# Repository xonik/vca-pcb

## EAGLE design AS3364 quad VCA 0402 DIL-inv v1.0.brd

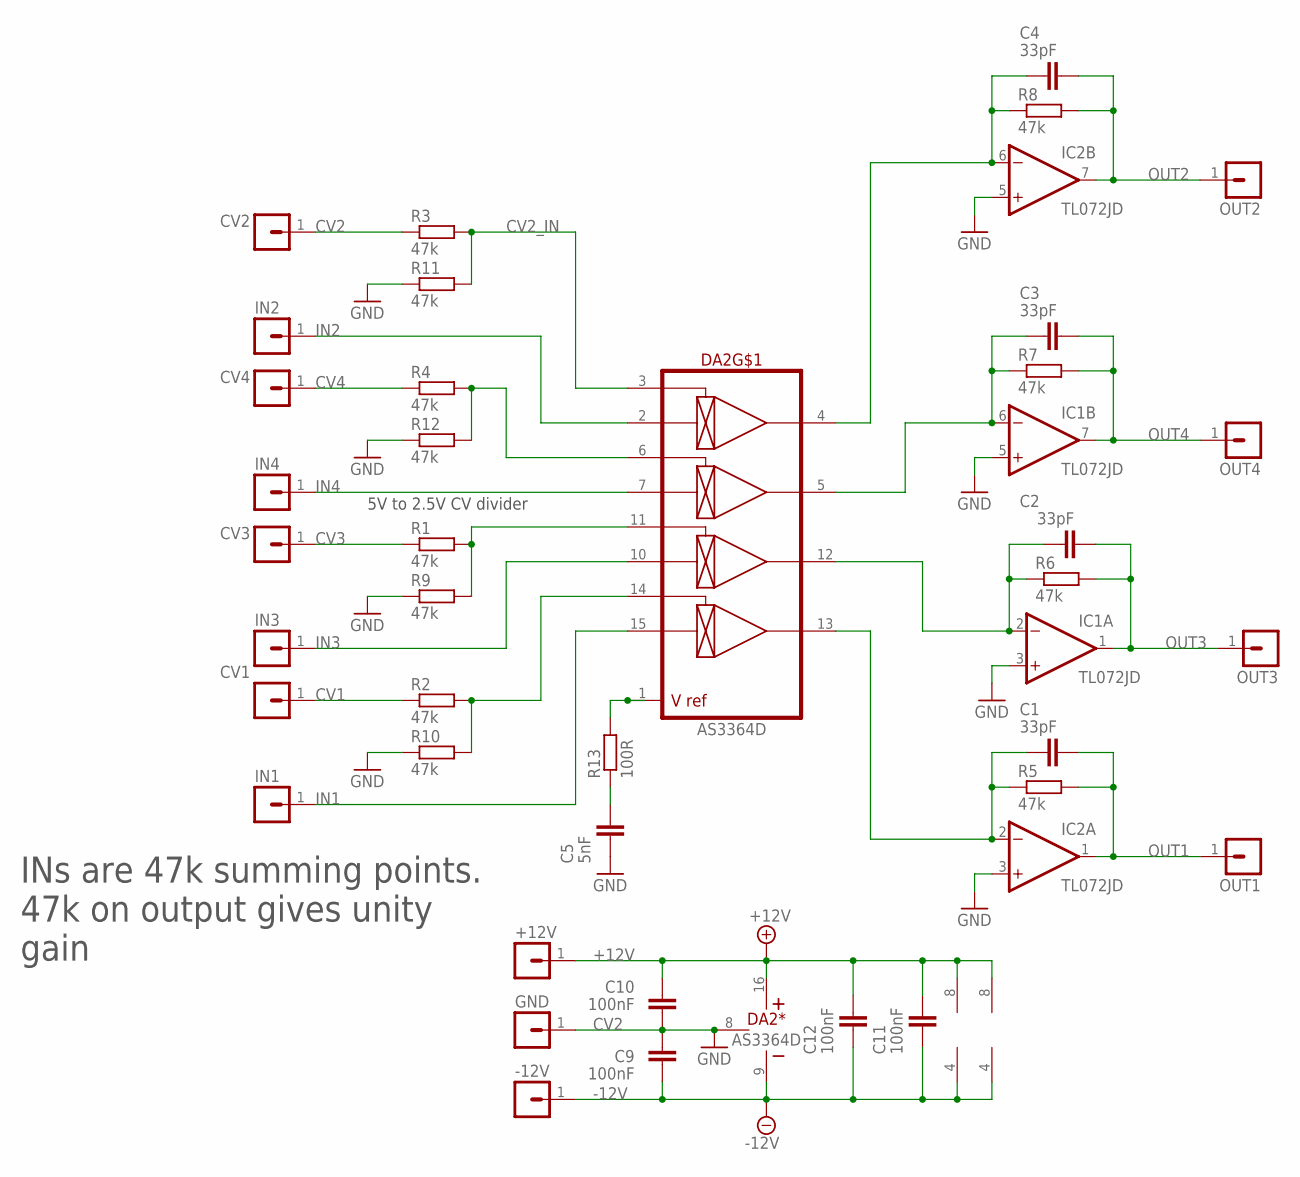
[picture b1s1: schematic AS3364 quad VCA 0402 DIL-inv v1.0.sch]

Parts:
+12V: MA01-1JP; SIP-PIN01-1J
-12V: MA01-1JP; SIP-PIN01-1J
C1, C2, C3, C4: 33pF; C0402
C5: 5nF; C0402
C9, C10, C11, C12: 100nF; C0402
CV1, CV2, CV3, CV4: MA01-1JP; SIP-PIN01-1J
DA2: AS3364D; DIL16J
GND: MA01-1JP; SIP-PIN01-1J
IC1, IC2: TL072JD; SO08J
IN1, IN2, IN3, IN4: MA01-1JP; SIP-PIN01-1J
OUT1, OUT2, OUT3, OUT4: MA01-1JP; SIP-PIN01-1J
R1, R2, R3, R4, R5, R6, R7, R8, R9, R10, R11, R12: 47k; R0402
R13: 100R; R0402

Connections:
+12V: +12V.1, C10.2, C11.2, C12.2, DA2.16 (V+), IC1.8 (V+), IC2.8 (V+)
-12V: -12V.1, C9.1, C11.1, C12.1, DA2.9 (V-), IC1.4 (V-), IC2.4 (V-)
CV1: CV1.1, R2.1
CV2: CV2.1, R3.1
CV2_IN: DA2.3 (CV1), R3.2, R11.2
CV3: CV3.1, R1.1
CV4: CV4.1, R4.1
GND: C5.1, C9.2, C10.1, DA2.8 (GND), GND.1, IC1.3 (+IN), IC1.5 (+IN), IC2.3 (+IN), IC2.5 (+IN), R9.1, R10.1, R11.1, R12.1
IN1: DA2.15 (IN4), IN1.1
IN2: DA2.2 (IN1), IN2.1
IN3: DA2.10 (IN3), IN3.1
IN4: DA2.7 (IN2), IN4.1
unnamed: C4.1, DA2.4 (OUT1), IC2.6 (-IN), R8.1
unnamed: DA2.1 (VREF), R13.2
unnamed: C3.1, DA2.5 (OUT2), IC1.6 (-IN), R7.1
unnamed: C2.1, DA2.12 (OUT3), IC1.2 (-IN), R6.1
unnamed: C1.1, DA2.13 (OUT4), IC2.2 (-IN), R5.1
unnamed: DA2.6 (CV2), R4.2, R12.2
unnamed: DA2.11 (CV3), R1.2, R9.2
unnamed: C5.2, R13.1
unnamed: DA2.14 (CV4), R2.2, R10.2
OUT1: C1.2, IC2.1 (OUT), OUT1.1, R5.2
OUT2: C4.2, IC2.7 (OUT), OUT2.1, R8.2
OUT3: C2.2, IC1.1 (OUT), OUT3.1, R6.2
OUT4: C3.2, IC1.7 (OUT), OUT4.1, R7.2

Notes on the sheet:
INs are 47k summing points. 47k on output gives unity gain
5V to 2.5V CV divider

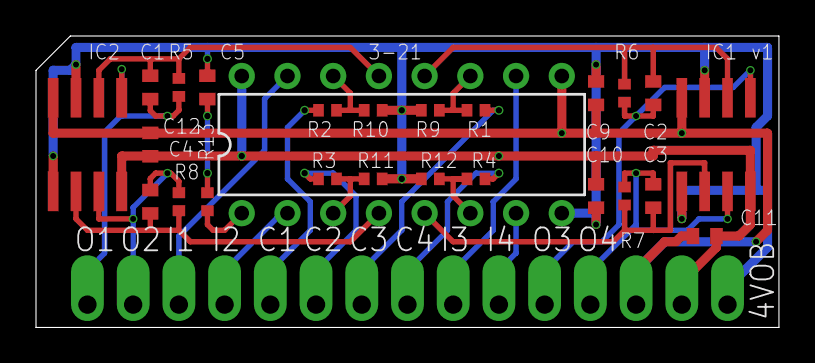
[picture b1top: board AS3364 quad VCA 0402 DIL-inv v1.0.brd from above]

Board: 2 copper layers, 41.3 x 16.2 mm, 41 parts (1 on the bottom side), 25 nets.

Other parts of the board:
U$1: XONIK_LOGO_18

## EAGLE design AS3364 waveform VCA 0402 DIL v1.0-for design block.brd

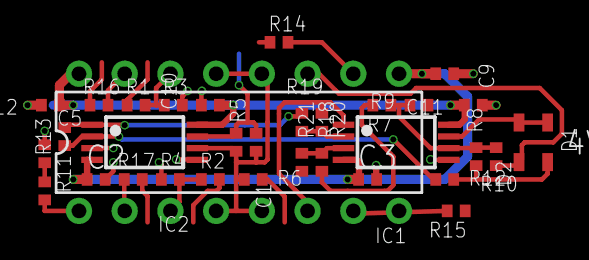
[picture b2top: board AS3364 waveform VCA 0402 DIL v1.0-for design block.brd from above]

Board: 2 copper layers, 35 parts (1 on the bottom side), 23 nets.

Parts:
C1: 33pF; C0402-J
C2, C3, C9, C10, C11, C12: 1uF; C0402-J
C5: 5nF; C0402-J
D1, D2: SOD323J
DA2: AS3364D; DIL16J
IC1, IC2: TL072JT; TSSOP8J
R1, R2: 33k; R0402
R3, R4: 22k; R0402
R5, R6, R14, R15, R16, R17: 47k; R0402
R7, R11, R18, R19: 25k; R0402
R8, R10, R20, R21: 20k; R0402
R9: 50k; R0402
R12: 10k; R0402
R13: 100R; R0402
U$1: XONIK_LOGO_18

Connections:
+12V: C10.2, C11.2, C12.2, DA2.16, IC1.8, IC2.8
-12V: C2.1, C3.1, C9.1, DA2.9, IC1.4, IC2.4
AGND: C2.2, C3.2, C5.1, C9.2, C10.1, C11.1, C12.1, DA2.8, IC1.5, IC2.3, IC2.5, R3.1, R4.1, R21.1
MIX_BUS: C1.2, DA2.4, DA2.5, DA2.12, DA2.13, IC2.6, R5.2, R6.1
unnamed: DA2.1, R13.2
unnamed: D1.1, D2.2, IC1.7
unnamed: IC1.6, R7.2, R8.1, R9.2, R10.1
unnamed: IC1.3, R18.2, R21.2
unnamed: C5.2, R13.1
unnamed: IC1.2, R19.2, R20.1
unnamed: IC2.2, R11.1, R12.2
unnamed: D1.2, R8.2, R12.1
OUT: C1.1, IC2.7, R5.1
PAN_CV: R7.1, R18.1
PULSE_CV: IC2.1, R11.2, R19.1
SAW_CV: DA2.6, IC1.1, R20.2
SAW_IN: DA2.7, R15.2
SUB1_CV_IN: DA2.14, R1.2, R3.2
SUB1_IN: DA2.15, R16.2
SUB2_CV_IN: DA2.3, R2.2, R4.2
SUB2_IN: DA2.2, R17.2
TRI_CV: D2.1, DA2.11, R10.2
TRI_IN: DA2.10, R14.2

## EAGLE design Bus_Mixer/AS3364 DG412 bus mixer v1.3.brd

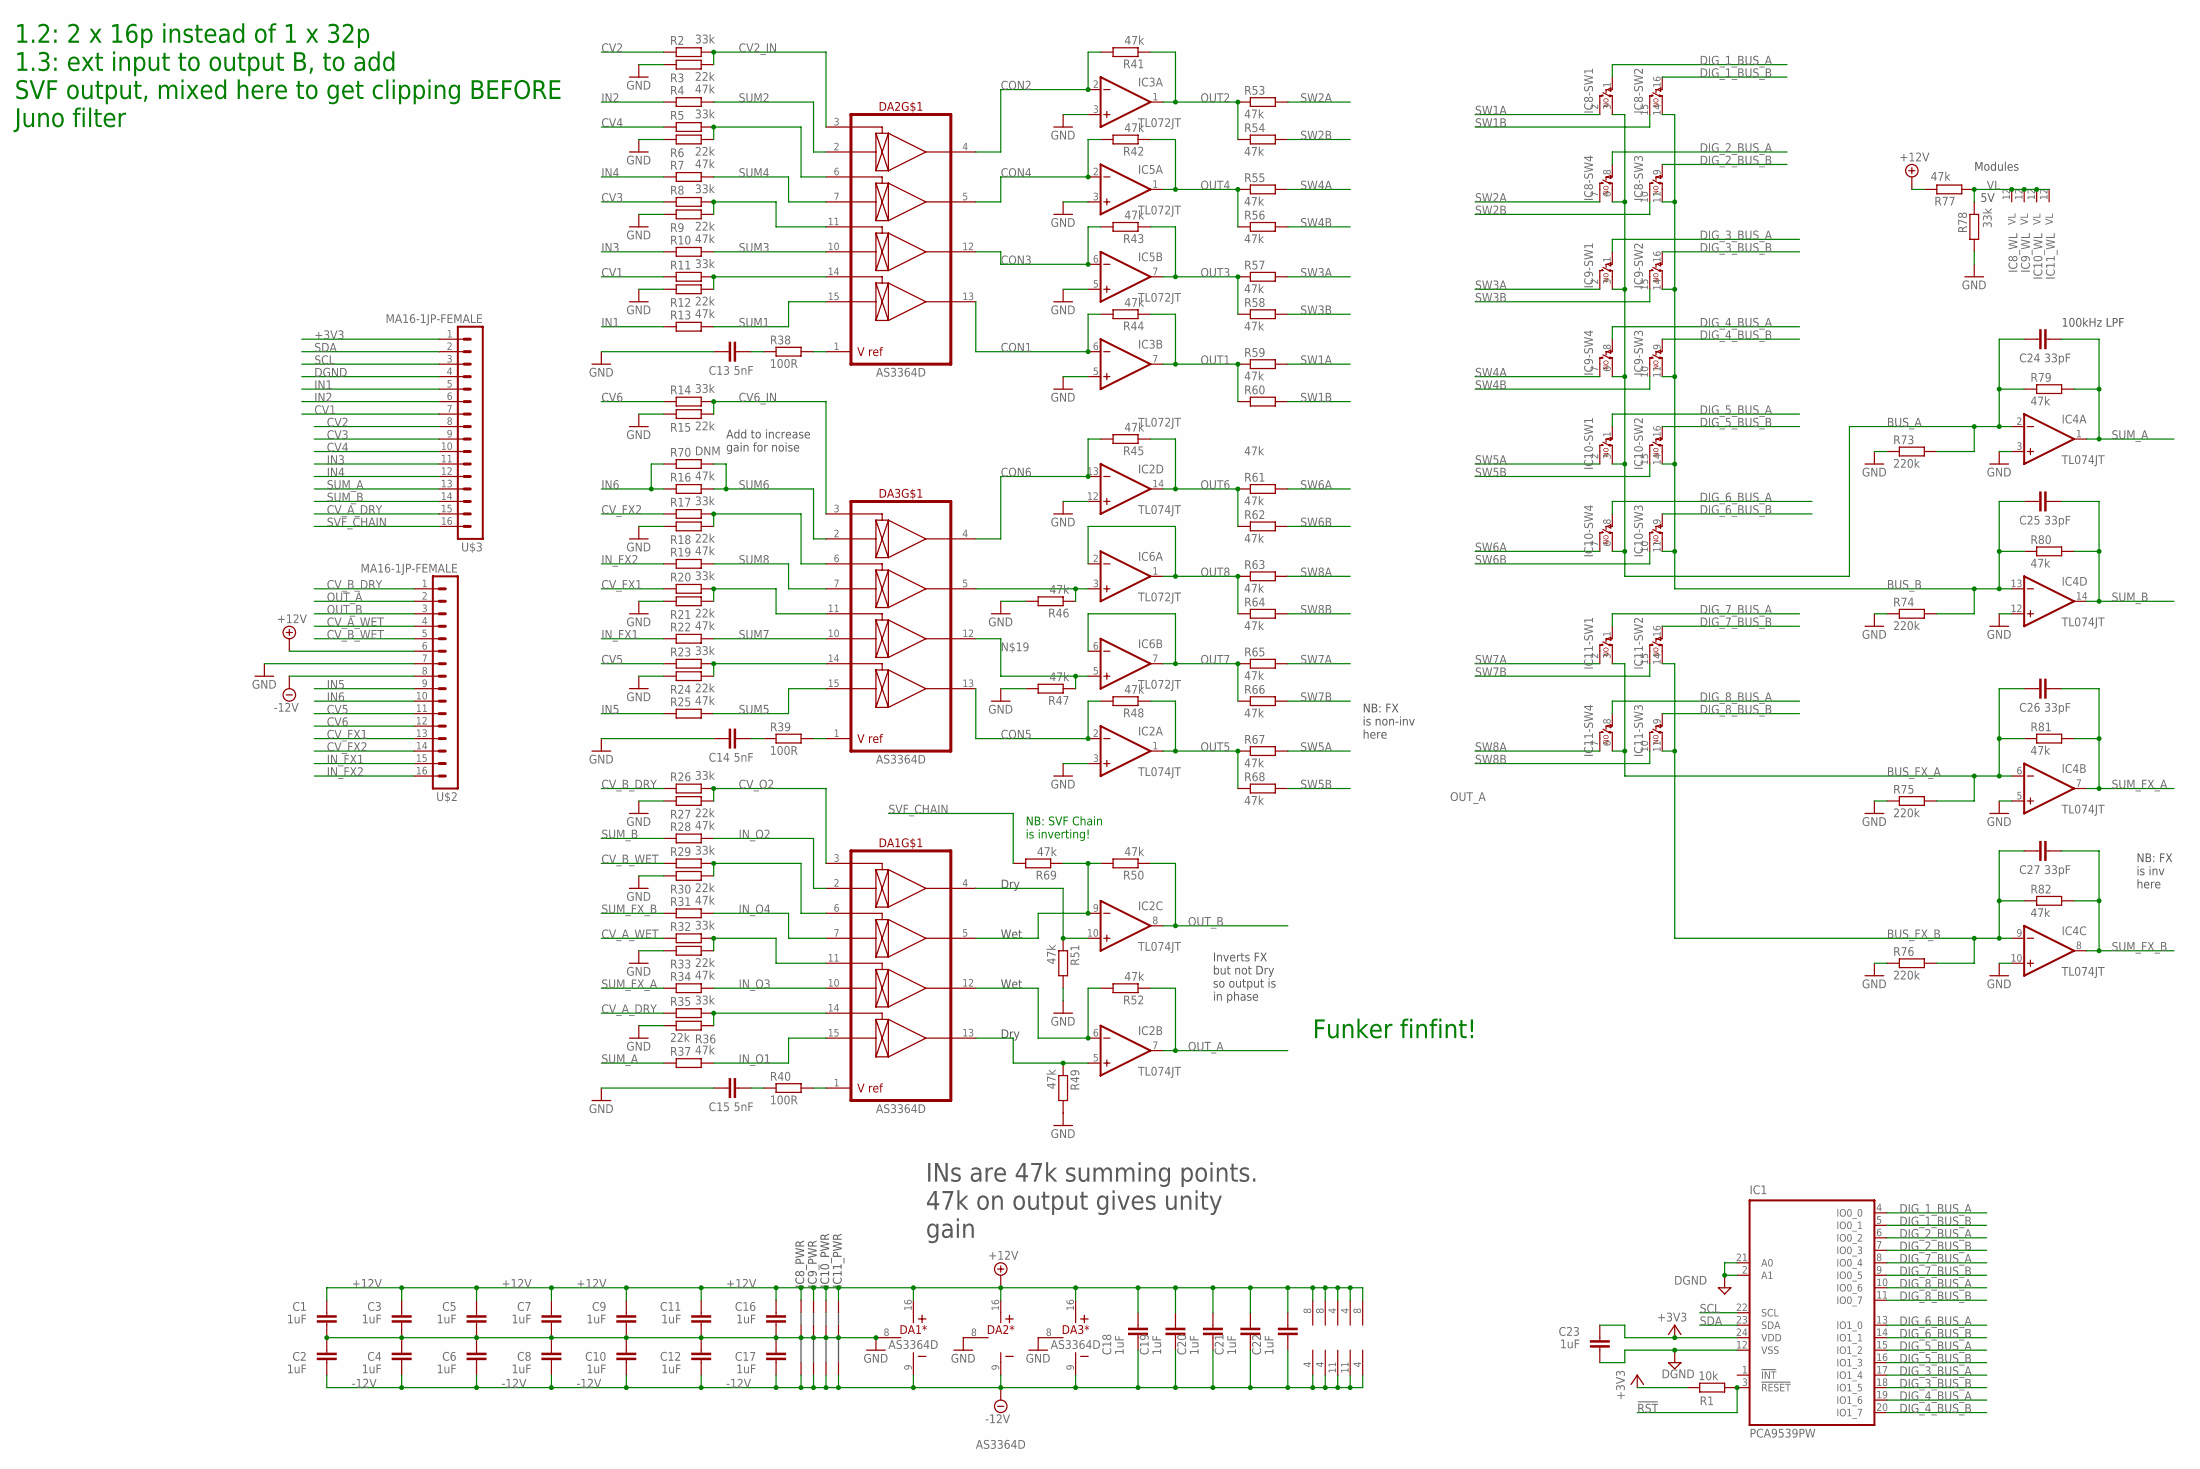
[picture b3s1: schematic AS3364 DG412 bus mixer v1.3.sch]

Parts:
C1, C2, C3, C4, C5, C6, C7, C8, C9, C10, C11, C12, C16, C17: 1uF; C0402-J
C13, C14, C15: 5nF; C0402-J
C18, C19, C20, C21, C22, C23: 1uF; C0402
C24, C25, C26, C27: 33pF; C0402-J
DA1, DA2, DA3: AS3364D; DIL16J
IC1: PCA9539PW; TSSOP24J
IC2, IC4: TL074JT; TSSOP14J
IC3, IC5, IC6: TL072JT; TSSOP8J
IC8, IC9, IC10, IC11: DG412-J; DIL16J
R1: 10k; R0402
R2, R5, R8, R11, R14, R17, R20, R23, R26, R29, R32, R35, R78: 33k; R0402
R3, R6, R9, R12, R15, R18, R21, R24, R27, R30, R33, R36: 22k; R0402
R4, R7, R10, R13, R16, R19, R22, R25, R28, R31, R34, R37, R41, R42, R43, R44, R45, R46, R47, R48, R49, R50, R51, R52, R53, R54, R55, R56, R57, R58, R59, R60, R61, R62, R63, R64, R65, R66, R67, R68, R69, R77, R79, R80, R81, R82: 47k; R0402
R38, R39, R40: 100R; R0402
R70: DNM; R0805
R73, R74, R75, R76: 220k; R0603
U$2, U$3: MA16-1JP-FEMALE; SIP-PIN16-1J

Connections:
!RST: IC1.3 (!RESET), R1.2
+3V3: C23.2, IC1.24 (VDD), R1.1, U$3.1
+12V: C1.2, C3.2, C5.2, C7.2, C9.2, C11.2, C16.2, C18.2, C19.2, C20.2, C21.2, C22.2, DA1.16 (V+), DA2.16 (V+), DA3.16 (V+), IC2.4 (V+), IC3.8 (V+), IC4.4 (V+), IC5.8 (V+), IC6.8 (V+), IC8.13 (+15V), IC9.13 (+15V), IC10.13 (+15V), IC11.13 (+15V), R77.1, U$2.6
-12V: C2.1, C4.1, C6.1, C8.1, C10.1, C12.1, C17.1, C18.1, C19.1, C20.1, C21.1, C22.1, DA1.9 (V-), DA2.9 (V-), DA3.9 (V-), IC2.11 (V-), IC3.4 (V-), IC4.11 (V-), IC5.4 (V-), IC6.4 (V-), IC8.4 (-15V), IC9.4 (-15V), IC10.4 (-15V), IC11.4 (-15V), U$2.8
BUS_A: C24.1, IC4.2 (-IN), IC8.3 (S), IC8.6 (S), IC9.3 (S), IC9.6 (S), IC10.3 (S), IC10.6 (S), R73.2, R79.1
BUS_B: C25.1, IC4.13 (-IN), IC8.11 (S), IC8.14 (S), IC9.11 (S), IC9.14 (S), IC10.11 (S), IC10.14 (S), R74.2, R80.1
BUS_FX_A: C26.1, IC4.6 (-IN), IC11.3 (S), IC11.6 (S), R75.2, R81.1
BUS_FX_B: C27.1, IC4.9 (-IN), IC11.11 (S), IC11.14 (S), R76.2, R82.1
CON1: DA2.13 (OUT4), IC3.6 (-IN), R44.2
CON2: DA2.4 (OUT1), IC3.2 (-IN), R41.2
CON3: DA2.12 (OUT3), IC5.6 (-IN), R43.2
CON4: DA2.5 (OUT2), IC5.2 (-IN), R42.2
CON5: DA3.13 (OUT4), IC2.2 (-IN), R48.2
CON6: DA3.4 (OUT1), IC2.13 (-IN), R45.2
CON_O1: DA1.12 (OUT3), IC2.6 (-IN), R52.2
CV1: R11.1, U$3.7
CV2: R2.1, U$3.8
CV2_IN: DA2.3 (CV1), R2.2, R3.2
CV3: R8.1, U$3.9
CV4: R5.1, U$3.10
CV5: R23.1, U$2.11
CV6: R14.1, U$2.12
CV6_IN: DA3.3 (CV1), R14.2, R15.2
CV_A_DRY: R35.1, U$3.15
CV_A_WET: R32.1, U$2.4
CV_B_DRY: R26.1, U$2.1
CV_B_WET: R29.1, U$2.5
CV_FX1: R20.1, U$2.13
CV_FX2: R17.1, U$2.14
CV_O2: DA1.3 (CV1), R26.2, R27.2
DGND: C23.1, IC1.2 (A1), IC1.12 (VSS), IC1.21 (A0), U$3.4
DIG_1_BUS_A: IC1.4 (IO0_0), IC8.1 (C)
DIG_1_BUS_B: IC1.5 (IO0_1), IC8.16 (C)
DIG_2_BUS_A: IC1.6 (IO0_2), IC8.8 (C)
DIG_2_BUS_B: IC1.7 (IO0_3), IC8.9 (C)
DIG_3_BUS_A: IC1.17 (IO1_4), IC9.1 (C)
DIG_3_BUS_B: IC1.18 (IO1_5), IC9.16 (C)
DIG_4_BUS_A: IC1.19 (IO1_6), IC9.8 (C)
DIG_4_BUS_B: IC1.20 (IO1_7), IC9.9 (C)
DIG_5_BUS_A: IC1.15 (IO1_2), IC10.1 (C)
DIG_5_BUS_B: IC1.16 (IO1_3), IC10.16 (C)
DIG_6_BUS_A: IC1.13 (IO1_0), IC10.8 (C)
DIG_6_BUS_B: IC1.14 (IO1_1), IC10.9 (C)
DIG_7_BUS_A: IC1.8 (IO0_4), IC11.1 (C)
DIG_7_BUS_B: IC1.9 (IO0_5), IC11.16 (C)
DIG_8_BUS_A: IC1.10 (IO0_6), IC11.8 (C)
DIG_8_BUS_B: IC1.11 (IO0_7), IC11.9 (C)
GND: C1.1, C2.2, C3.1, C4.2, C5.1, C6.2, C7.1, C8.2, C9.1, C10.2, C11.1, C12.2, C13.1, C14.1, C15.1, C16.1, C17.2, DA1.8 (GND), DA2.8 (GND), DA3.8 (GND), IC2.3 (+IN), IC2.12 (+IN), IC3.3 (+IN), IC3.5 (+IN), IC4.3 (+IN), IC4.5 (+IN), IC4.10 (+IN), IC4.12 (+IN), IC5.3 (+IN), IC5.5 (+IN), IC8.5 (AGND), IC9.5 (AGND), IC10.5 (AGND), IC11.5 (AGND), R3.1, R6.1, R9.1, R12.1, R15.1, R18.1, R21.1, R24.1, R27.1, R30.1, R33.1, R36.1, R46.2, R47.2, R49.2, R51.2, R73.1, R74.1, R75.1, R76.1, R78.2, U$2.7
IN1: R13.1, U$3.5
IN2: R4.1, U$3.6
IN3: R10.1, U$3.11
IN4: R7.1, U$3.12
IN5: R25.1, U$2.9
IN6: R16.1, R70.1, U$2.10
IN_FX1: R22.1, U$2.15
IN_FX2: R19.1, U$2.16
IN_O1: DA1.15 (IN4), R37.2
IN_O2: DA1.2 (IN1), R28.2
IN_O3: DA1.10 (IN3), R34.2
IN_O4: DA1.7 (IN2), R31.2
unnamed: DA3.1 (VREF), R39.2
unnamed: DA2.1 (VREF), R38.2
unnamed: DA3.6 (CV2), R17.2, R18.2
unnamed: DA3.5 (OUT2), IC6.3 (+IN), R46.1
unnamed: DA3.11 (CV3), R20.2, R21.2
unnamed: DA1.5 (OUT2), IC2.9 (-IN), R50.2, R69.1
unnamed: DA3.14 (CV4), R23.2, R24.2
unnamed: C14.2, R39.1
unnamed: DA1.1 (VREF), R40.2
unnamed: DA2.6 (CV2), R5.2, R6.2
unnamed: DA1.6 (CV2), R29.2, R30.2
unnamed: DA2.11 (CV3), R8.2, R9.2
unnamed: DA1.11 (CV3), R32.2, R33.2
unnamed: C13.2, R38.1
unnamed: DA1.14 (CV4), R35.2, R36.2
unnamed: C15.2, R40.1
unnamed: DA1.4 (OUT1), IC2.10 (+IN), R51.1
unnamed: DA1.13 (OUT4), IC2.5 (+IN), R49.1
unnamed: DA3.12 (OUT3), IC6.5 (+IN), R47.1
unnamed: DA2.14 (CV4), R11.2, R12.2
OUT1: IC3.7 (OUT), R44.1, R59.1, R60.1
OUT2: IC3.1 (OUT), R41.1, R53.1, R54.1
OUT3: IC5.7 (OUT), R43.1, R57.1, R58.1
OUT4: IC5.1 (OUT), R42.1, R55.1, R56.1
OUT5: IC2.1 (OUT), R48.1, R67.1, R68.1
OUT6: IC2.14 (OUT), R45.1, R61.1, R62.1
OUT7: IC6.6 (-IN), IC6.7 (OUT), R65.1, R66.1
OUT8: IC6.1 (OUT), IC6.2 (-IN), R63.1, R64.1
OUT_A: IC2.7 (OUT), R52.1, U$2.2
OUT_B: IC2.8 (OUT), R50.1, U$2.3
SCL: IC1.22 (SCL), U$3.3
SDA: IC1.23 (SDA), U$3.2
SUM1: DA2.15 (IN4), R13.2
SUM2: DA2.2 (IN1), R4.2
SUM3: DA2.10 (IN3), R10.2
SUM4: DA2.7 (IN2), R7.2
SUM5: DA3.15 (IN4), R25.2
SUM6: DA3.2 (IN1), R16.2, R70.2
SUM7: DA3.10 (IN3), R22.2
SUM8: DA3.7 (IN2), R19.2
SUM_A: C24.2, IC4.1 (OUT), R37.1, R79.2, U$3.13
SUM_B: C25.2, IC4.14 (OUT), R28.1, R80.2, U$3.14
SUM_FX_A: C26.2, IC4.7 (OUT), R34.1, R81.2
SUM_FX_B: C27.2, IC4.8 (OUT), R31.1, R82.2
SVF_CHAIN: R69.2, U$3.16
SW1A: IC8.2 (D), R59.2
SW1B: IC8.15 (D), R60.2
SW2A: IC8.7 (D), R53.2
SW2B: IC8.10 (D), R54.2
SW3A: IC9.2 (D), R57.2
SW3B: IC9.15 (D), R58.2
SW4A: IC9.7 (D), R55.2
SW4B: IC9.10 (D), R56.2
SW5A: IC10.2 (D), R67.2
SW5B: IC10.15 (D), R68.2
SW6A: IC10.7 (D), R61.2
SW6B: IC10.10 (D), R62.2
SW7A: IC11.2 (D), R65.2
SW7B: IC11.15 (D), R66.2
SW8A: IC11.7 (D), R63.2
SW8B: IC11.10 (D), R64.2
VL: IC8.12 (VL), IC9.12 (VL), IC10.12 (VL), IC11.12 (VL), R77.2, R78.1

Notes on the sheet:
INs are 47k summing points. 47k on output gives unity gain
Modules
100kHz LPF
Funker finfint!
Wet
Dry
NB: FX is non-inv here
NB: FX is inv here
Inverts FX but not Dry so output is in phase
1.2: 2 x 16p instead of 1 x 32p 1.3: ext input to output B, to add SVF output, mixed here to get clipping BEFORE Juno filter
NB: SVF Chain is inverting!
Add to increase gain for noise

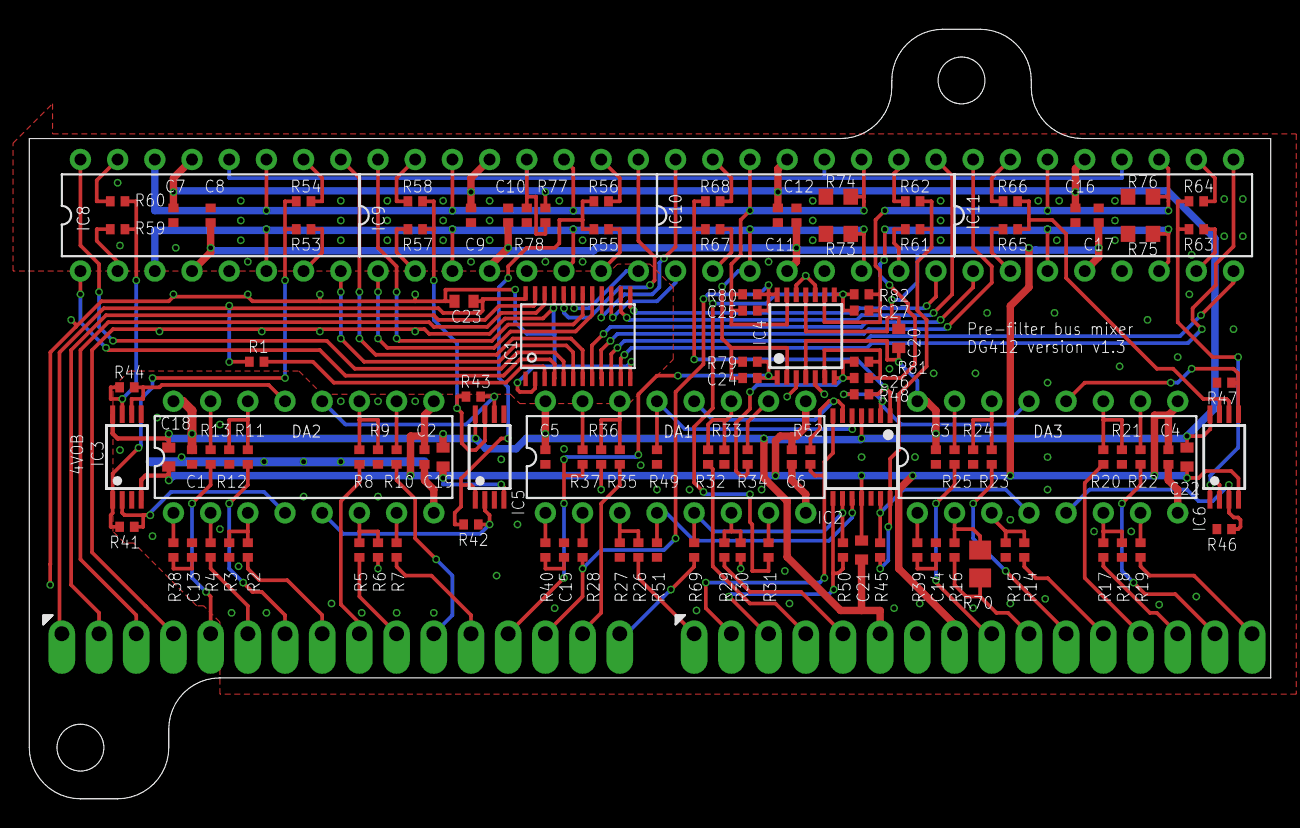
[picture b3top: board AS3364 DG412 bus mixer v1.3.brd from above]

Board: 2 copper layers, 84.8 x 52.5 mm, 123 parts (1 on the bottom side), 122 nets.

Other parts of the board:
U$1: XONIK_LOGO_35

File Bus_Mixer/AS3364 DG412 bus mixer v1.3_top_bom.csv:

Comment,Designator,Footprint,LCSC Part #
1uF,C1 C2 C3 C4 C5 C6 C7 C8 C9 C10 C11 C12 C16 C17,C0402-J,
1uF,C18 C19 C20 C21 C22 C23,C0402,
5nF,C13 C14 C15,C0402-J,
10k,R1,R0402,
22k,R3 R6 R9 R12 R15 R18 R21 R24 R27 R30 R33 R36,R0402,
33k,R2 R5 R8 R11 R14 R17 R20 R23 R26 R29 R32 R35 R78,R0402,
33pF,C24 C25 C26 C27,C0402-J,
47k,R4 R7 R10 R13 R16 R19 R22 R25 R28 R31 R34 R37 R41 R42 R43 R44 R45 R46 R47 R48 R49 R50 R51 R52 R53 R54 R55 R56 R57 R58 R59 R60 R61 R62 R63 R64 R65 R66 R67 R68 R69 R77 R79 R80 R81 R82,R0402,
100R,R38 R39 R40,R0402,
220k,R73 R74 R75 R76,R0603,
AS3364D,DA1 DA2 DA3,DIL16J,
DG412-J,IC8 IC9 IC10 IC11,DIL16J,
DNM,R70,R0805,
MA16-1JP-FEMALE,U$2 U$3,SIP-PIN16-1J,
PCA9539PW,IC1,TSSOP24J,
TL072JT,IC3 IC5 IC6,TSSOP8J,
TL074JT,IC2 IC4,TSSOP14J,
